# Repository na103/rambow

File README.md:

# RAMbow - 1Mbyte memory expansion for Rainbow 100
"RAMbow flexes memory muscle" was the headline of a hardware review in the Silicon Valley Rainbow bulletin in October 1987.<br>
The article, which you can read in full [here](https://github.com/na103/rambow/blob/main/docs/RAMbow.pdf), discusses a memory expansion designed by Jerry Miller and marketed by Suitable Solution.<br>
This expansion could extend the memory of the first version of the Rainbow 100 (revision A) beyond its design limit of 256KB.<br><br>

<br>
The Rainbow 100 initially came with only 64KB onboard, which could be expanded via the option RAM up to a maximum of 256KB.<br>
Later, DEC developed an 8087 adapter card that allowed the option RAM card of the Rainbow 100 B to be used in rev A, enabling memory expansion up to a maximum of 832KB with a sandwich installation.<br>
RAMbow combines the 8087 adapter and the option RAM of the Rainbow B into a single card, allowing 896KB of memory on the 100A.<br>
Inspired by this article, I modified [my remake of the option RAM rev. B](https://github.com/na103/rainbow100-memory) with a single 1MB DRAM bank, creating room to accommodate the 8088 CPU socket.<br>
Indeed the main problem with the 100A is that the expansion connector of the option RAM lacks the A16 to A19 address lines, necessitating the relocation of the CPU onto the memory card.<br>   
In this repository you will find all the information needed to build my interpretation of the legendary RAMbow (no schematics or picture exist the original board).<br>

## Bill of materials
| Qt. |    Description     |             Designator          |    Mouser Part     |             Note              |
|:---:|--------------------|---------------------------------|--------------------|-------------------------------|
|10   |Cap. 220 nF 50V     |C1-C9,C18                        |C430C224Z5U5TA      |                               |
|1    |Cap. 10uF 50V       |C17                              |MAL213831109E3      |                               |
|5    |Cap. 47nF 50V       |C12-C16                          |C410C473Z5U5TA      |                               |
|2    |Cap. 10nF 50V       |C10,C11                          |C410C103Z5U5TA      |                               |
|1    |Bead Ferrite        |FB1                              |2743002112          |                               |
|2    |Rnet 9x1kΩ 10 pin   |RN1,RN2                          |4610X-101-102LF     |                               |
|1    |Rnet 9x4.7kΩ 10 pin |RN3                              |4610X-AP1-472LF     |                               |
|10   |R 39Ω               |R2-R11                           |CFR-25JB-52-39R     |                               |
|3    |R 470Ω              |R12-R14                          |CFR-25JB-52-470R    |                               |
|1    |R 100Ω              |R1                               |CFR-25JR-52-100R    |                               |
|3    |R 47Ω               |R15-R17                          |CFR-25JB-52-47R     |                               |
|2    |2 pin header        |JP1,JP2                          |67996-102HLF        |                               |
|2    |2 pin jumper shunt  |JP1,JP2                          |SNT-100-BL-T        |                               |
|1    |025X025 REC 2X30P   |J1                               |5-102766-4          |                               |
|9    |18P DIP SKT         |E16-E24                          |1-2199298-5         |                               |
|1    |40P DIP SKT         |E26                              |1-2199299-5         |                               |
|1    |20P DIP SKT         |E28                              |1-2199298-6         |                               |
|1    |40P IDC CONN M      |J2                               |3-1761605-3         |                               |
|1    |40P DIP IDC SKT     |J2                               |CWR-130-40-0000     |                               |
|1    |40P IDC CONN F      |J2                               |D89140-0101HK       |                               |
|1    |40P IDC Flat cable  |J2                               |                    | you can use an old IDE cable  |
|1    |GAL 16V8            |E28                              |ATF16V8CZ-15PU      | need programmer like TL866    |
|2    |74LS04              |E1,E7                            |SN74LS04N           |                               |
|3    |74LS258             |E2,E3,E15                        |SN74LS258BN         |                               |
|2    |74LS393             |E4,E25                           |SN74LS393N          |                               |
|2    |74LS244             |E5,E14                           |SN74LS244N          |                               |
|1    |74LS245             |E6                               |SN7LS245N           |                               |
|1    |74LS27              |E8                               |SN74LS27N           |                               |
|1    |74LS280             |E9                               |SN74LS280N          |                               |
|1    |74LS125             |E10                              |SN74LS125AN         |                               |
|1    |74LS00              |E11                              |SN74LS00N           |                               |
|1    |74LS03              |E12                              |SN74LS03N           |                               |
|1    |74LS74              |E13                              |SN74LS74AN          |                               |
|1    |74LS373             |E27                              |SN74LS373N          |                               |
|9    |1Mbit DRAM 41024    |E16-E24                          |HM511000AP-8        | from ebay or [utsource](https://www.utsource.net)|

<br>

## Jumper set-up
Only a jumper need to setup, JP2 is closed when RAMbow is installed on rev A or open in rev B.<br>
JP1 is always closed.

## Building notes
As you can see from the picture the IDC cable of the J2 connector that is used to relocate the CPU requires a bit of attention in construction<br><br>
<br>
the length of the cable must be 85mm and you must separate the individual wires with a cutter to make the cable more flexible.<br>
the operation requires a little attention to avoid cutting the copper insulation.<br>
even closing the socket with pressure requires a fair amount of force, help yourself with some tool<br>

<br>

## Compatibility and issues

I have successfully tested RAMbow on rev. A and rev. B. with the following operating systems:<br>
MSDOS 3.10<br>
MSDOS 2.10<br>
CP/M-86/80 2.10<br>
CP/M-86/80 2.0<br>
I have not encountered any kind of problem, both rev A and rev B have 896Kb of memory available.<br>
After building RAMbow you can test it with the diagnostic software for memory expansion rev B that you can find [here](https://github.com/na103/rainbow100-memory/tree/main/software)<br><br>

## Thanks
Thankyou to all the people who have helped with this project.<br>
Bigfix for sharing the DEC schematics of the 8087 adapter.<br>
N. Brown and Alitel for actively participating with their ideas in the [VCFED forum thread.](https://forum.vcfed.org/index.php?threads/rainbow-100a-memory-beyond-256k.1247302/)<br>
Claudio Parmigiani for the valuable advice<br>

If you found this my work useful, please consider buying me a cup of coffee if you want:<br>

# License

This work is licensed under a Creative Commons Attribution 4.0 International License. See [https://creativecommons.org/licenses/by/4.0/](https://creativecommons.org/licenses/by/4.0/).

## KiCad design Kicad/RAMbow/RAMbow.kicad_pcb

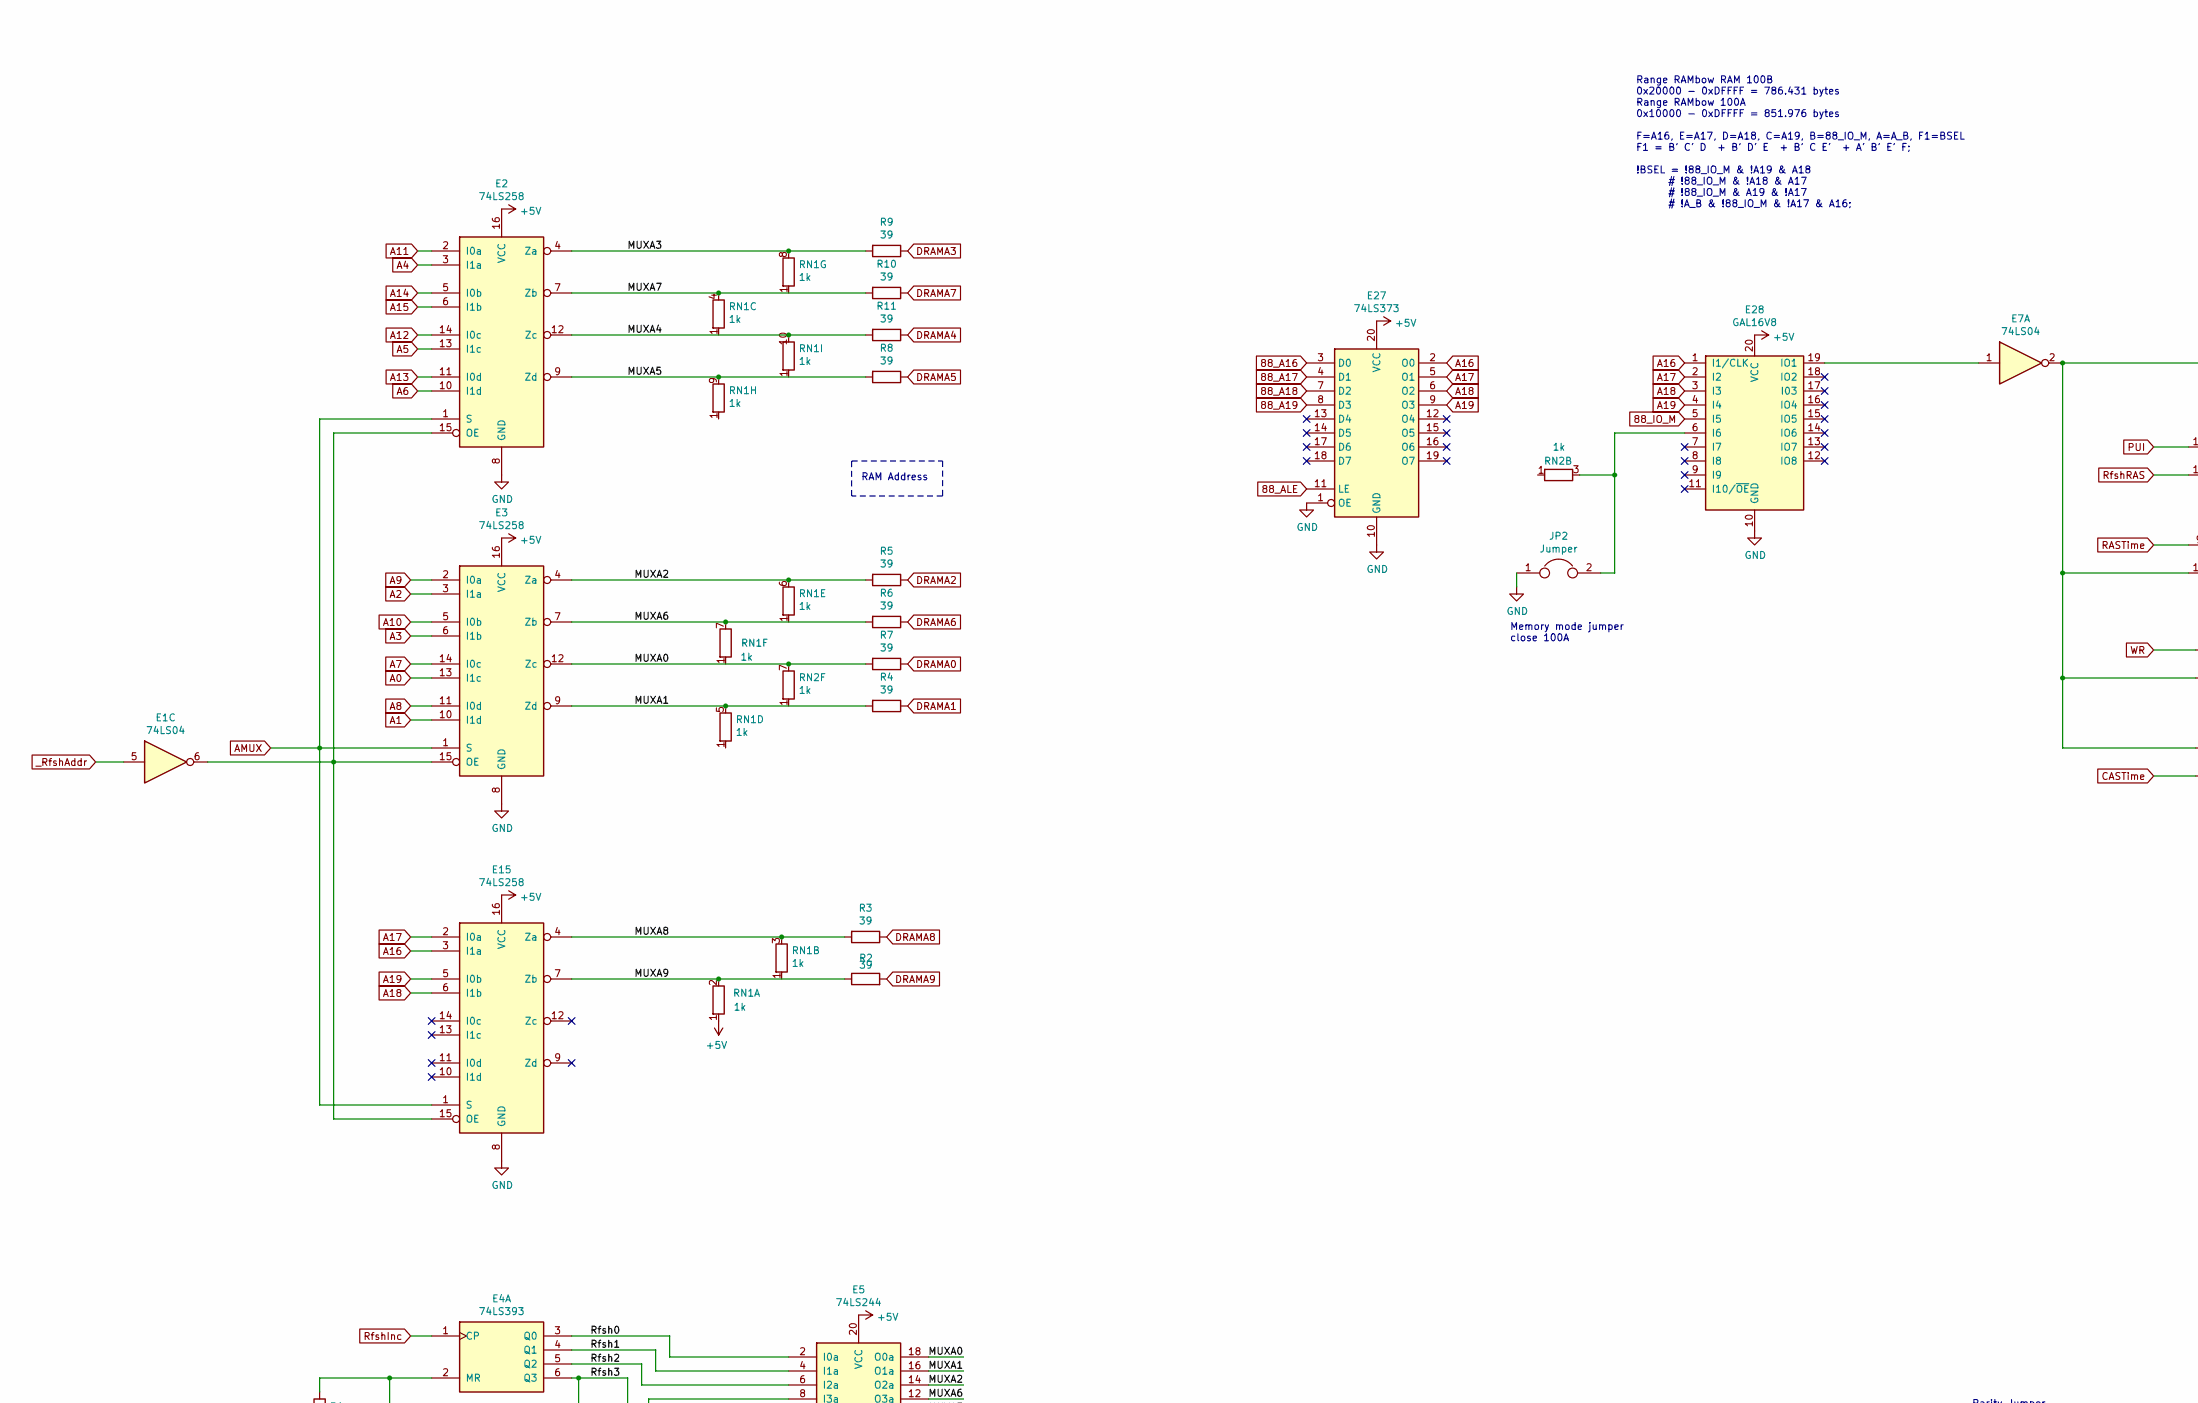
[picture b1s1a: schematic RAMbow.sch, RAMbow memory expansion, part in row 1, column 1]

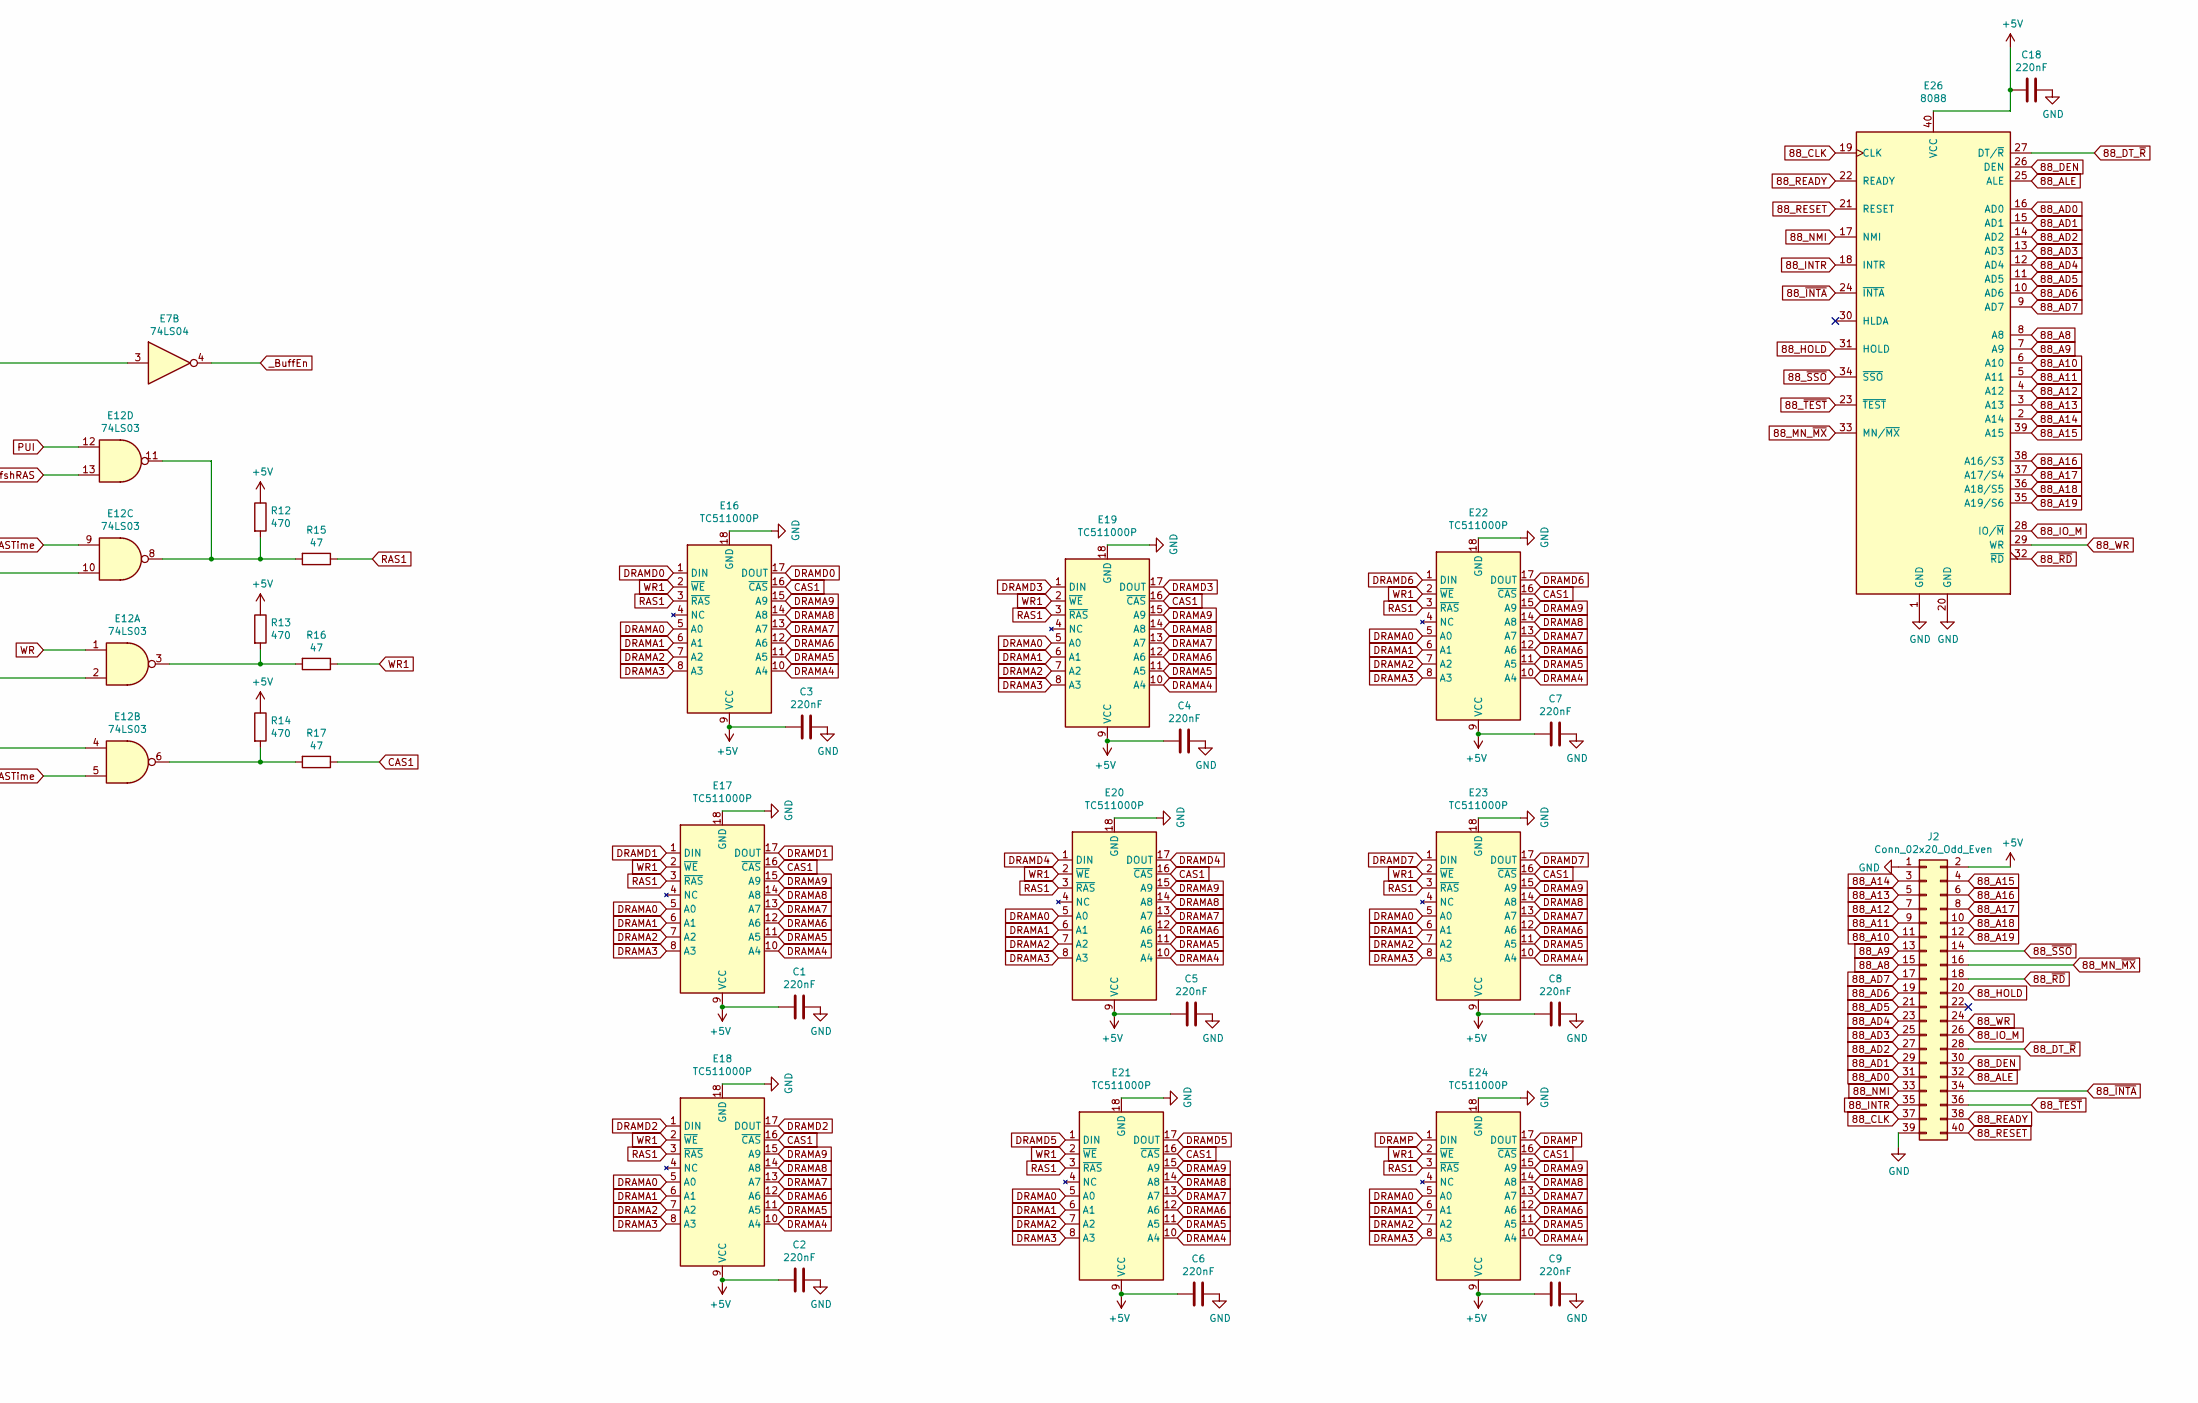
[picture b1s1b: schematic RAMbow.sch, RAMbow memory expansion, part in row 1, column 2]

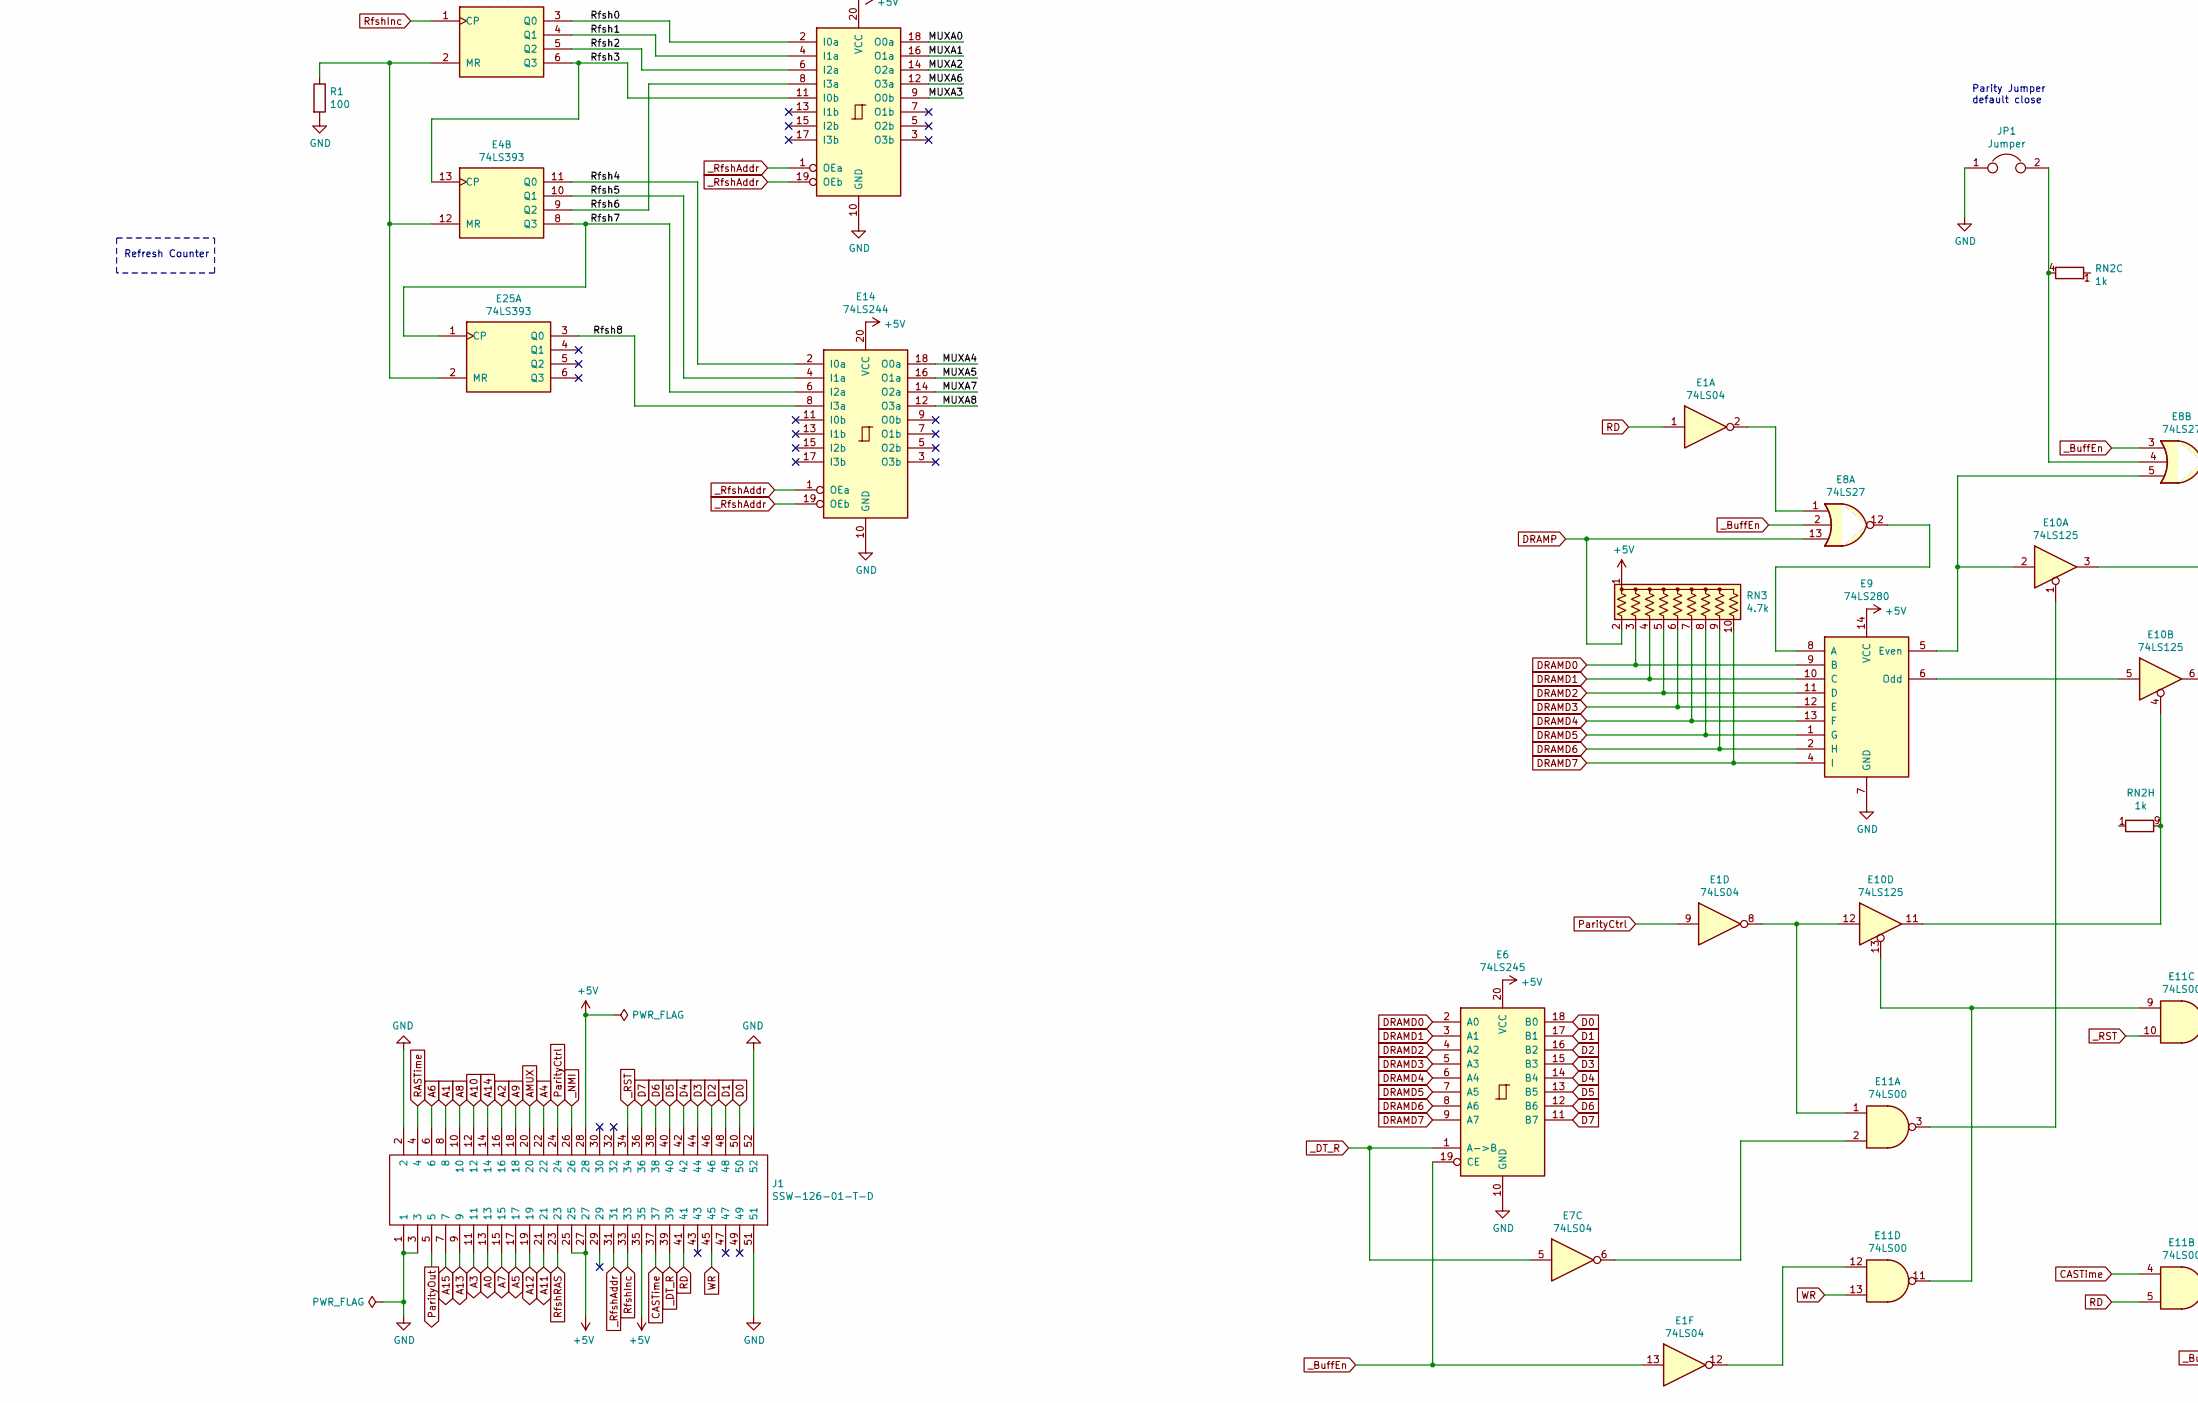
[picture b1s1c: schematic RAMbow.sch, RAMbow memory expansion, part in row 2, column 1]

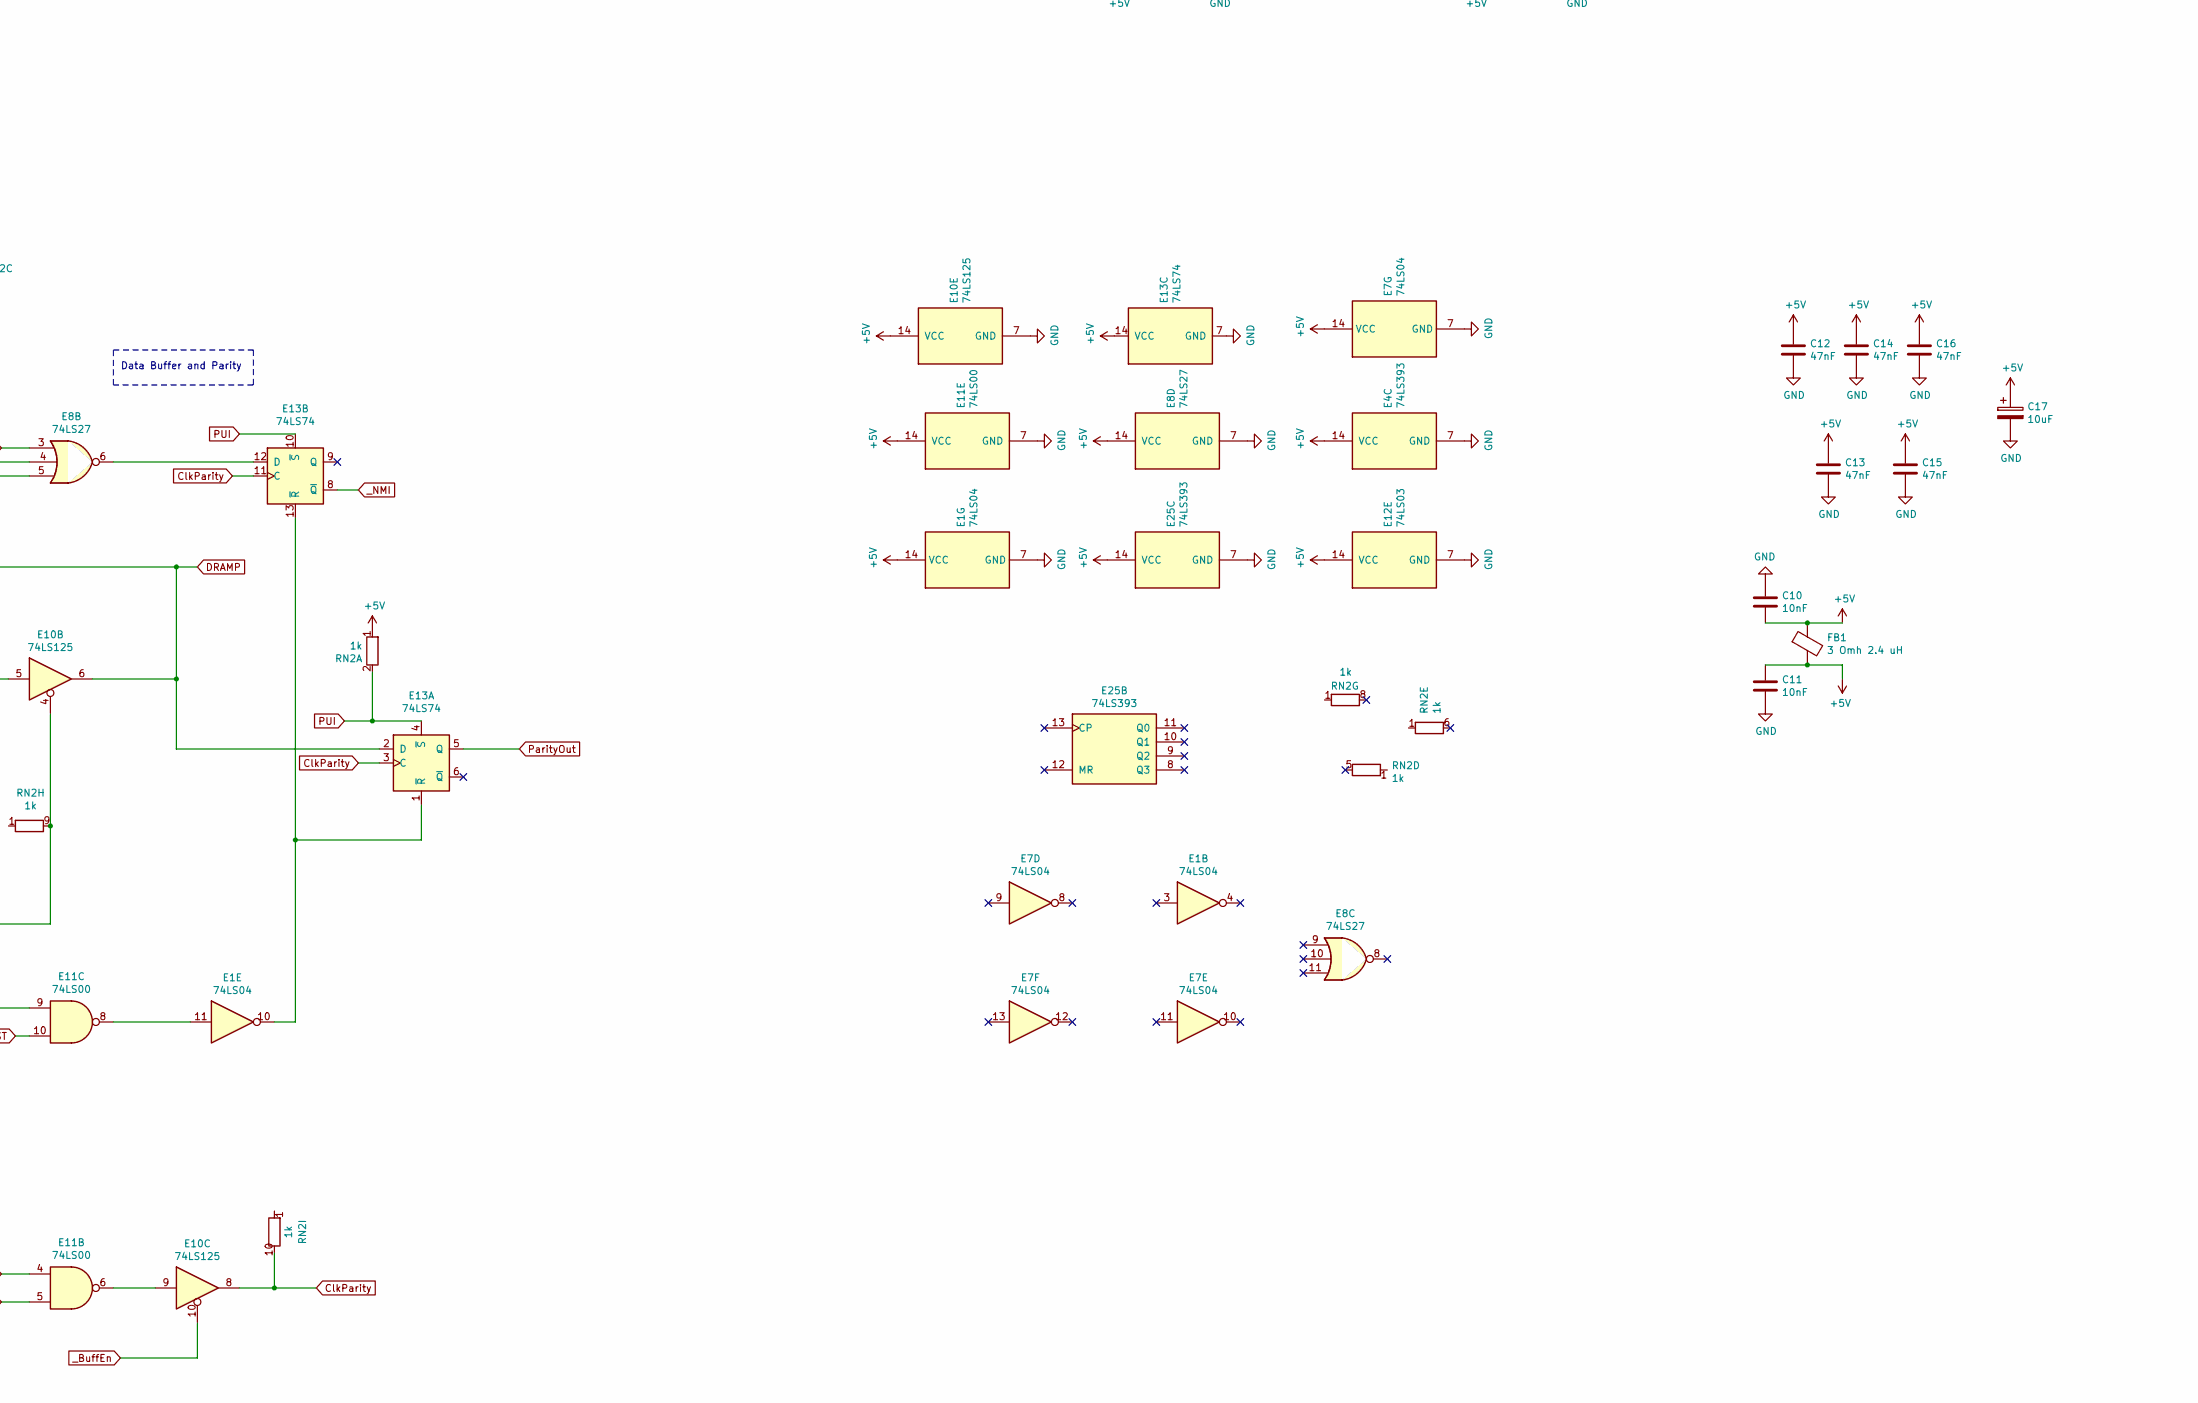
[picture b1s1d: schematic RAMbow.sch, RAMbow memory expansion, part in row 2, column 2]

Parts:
C1, C2, C3, C4, C5, C6, C7, C8, C9, C18: 220nF; C_Axial_L3.8mm_D2.6mm_P7.50mm_Horizontal
C10, C11: 10nF; C_Axial_L3.8mm_D2.6mm_P10.00mm_Horizontal
C12, C13, C14, C15, C16: 47nF; C_Axial_L3.8mm_D2.6mm_P10.00mm_Horizontal
C17: 10uF; C_Axial_L12.0mm_D6.5mm_P20.00mm_Horizontal
E1, E7: 74LS04; DIP-14_W7.62mm
E2, E3, E15: 74LS258; DIP-16_W7.62mm
E4, E25: 74LS393; DIP-14_W7.62mm
E5, E14: 74LS244; DIP-20_W7.62mm
E6: 74LS245; DIP-20_W7.62mm
E8: 74LS27; DIP-14_W7.62mm
E9: 74LS280; DIP-14_W7.62mm
E10: 74LS125; DIP-14_W7.62mm
E11: 74LS00; DIP-14_W7.62mm
E12: 74LS03; DIP-14_W7.62mm
E13: 74LS74; DIP-14_W7.62mm
E16, E17, E18, E19, E20, E21, E22, E23, E24: TC511000P; DIP-18_W7.62mm
E26: 8088; DIP-40_W15.24mm
E27: 74LS373; DIP-20_W7.62mm
E28: GAL16V8; DIP-20_W7.62mm
FB1: 3 Omh 2.4 uH; L_Axial_L9.5mm_D4.0mm_P15.24mm_Horizontal_Fastron_SMCC
J1: SSW-126-01-T-D; SAMTEC_SSW-126-01-T-D; Mouser Part Number 200-SSW12601TD
J2: Conn_02x20_Odd_Even; IDC-Header_2x20_P2.54mm_Horizontal
JP1, JP2: Jumper; PinHeader_1x02_P2.54mm_Vertical
R1: 100; R_Axial_DIN0207_L6.3mm_D2.5mm_P10.16mm_Horizontal
R2, R3, R4, R5, R6, R7, R8, R9, R10, R11: 39; R_Axial_DIN0207_L6.3mm_D2.5mm_P10.16mm_Horizontal
R12, R13, R14: 470; R_Axial_DIN0207_L6.3mm_D2.5mm_P10.16mm_Horizontal
R15, R16, R17: 47; R_Axial_DIN0207_L6.3mm_D2.5mm_P10.16mm_Horizontal
RN1, RN2: 1k; R_Array_SIP10
RN3: 4.7k; R_Array_SIP10

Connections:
88_A8: E26.8 (A8), J2.15
88_A9: E26.7 (A9), J2.13
88_A10: E26.6 (A10), J2.11
88_A11: E26.5 (A11), J2.9
88_A12: E26.4 (A12), J2.7
88_A13: E26.3 (A13), J2.5
88_A14: E26.2 (A14), J2.3
88_A15: E26.39 (A15), J2.4
88_A16: E26.38 (A16/S3), E27.3 (D0), J2.6
88_A17: E26.37 (A17/S4), E27.4 (D1), J2.8
88_A18: E26.36 (A18/S5), E27.7 (D2), J2.10
88_A19: E26.35 (A19/S6), E27.8 (D3), J2.12
88_AD0: E26.16 (AD0), J2.31
88_AD1: E26.15 (AD1), J2.29
88_AD2: E26.14 (AD2), J2.27
88_AD3: E26.13 (AD3), J2.25
88_AD4: E26.12 (AD4), J2.23
88_AD5: E26.11 (AD5), J2.21
88_AD6: E26.10 (AD6), J2.19
88_AD7: E26.9 (AD7), J2.17
88_ALE: E26.25 (ALE), E27.11 (LE), J2.32
88_CLK: E26.19 (CLK), J2.37
88_DEN: E26.26 (DEN), J2.30
88_DT_~R~: E26.27 (DT/~R~), J2.28
88_HOLD: E26.31 (HOLD), J2.20
88_INTR: E26.18 (INTR), J2.35
88_IO_M: E26.28 (IO/~M~), E28.5 (I5), J2.26
88_MN_~MX~: E26.33 (MN/~MX~), J2.16
88_NMI: E26.17 (NMI), J2.33
88_READY: E26.22 (READY), J2.38
88_RESET: E26.21 (RESET), J2.40
88_WR: E26.29 (WR), J2.24
88_~INTA~: E26.24 (~INTA~), J2.34
88_~RD~: E26.32 (~RD~), J2.18
88_~SSO~: E26.34 (~SSO~), J2.14
88_~TEST~: E26.23 (~TEST~), J2.36
+5V: C1.2, C2.2, C3.2, C4.2, C5.2, C6.2, C7.2, C8.2, C9.2, C10.2, C11.1, C12.1, C13.1, C14.1, C15.1, C16.1, C17.1, C18.2, E1.14 (VCC), E2.16 (VCC), E3.16 (VCC), E4.14 (VCC), E5.20 (VCC), E6.20 (VCC), E7.14 (VCC), E8.14 (VCC), E9.14 (VCC), E10.14 (VCC), E11.14 (VCC), E12.14 (VCC), E13.14 (VCC), E14.20 (VCC), E15.16 (VCC), E16.9 (VCC), E17.9 (VCC), E18.9 (VCC), E19.9 (VCC), E20.9 (VCC), E21.9 (VCC), E22.9 (VCC), E23.9 (VCC), E24.9 (VCC), E25.14 (VCC), E26.40 (VCC), E27.20 (VCC), E28.20 (VCC), FB1.1, FB1.2, J1.25, J1.27, J1.28, J1.35, J2.2, R12.1, R13.1, R14.1, RN1.1 (R1.1), RN2.1 (R1.1), RN3.1 (common)
/MUXA0: E3.12 (Zc), E5.18 (O0a), R7.2, RN2.7 (R6.2)
/MUXA1: E3.9 (Zd), E5.16 (O1a), R4.2, RN1.5 (R4.2)
/MUXA2: E3.4 (Za), E5.14 (O2a), R5.2, RN1.6 (R5.2)
/MUXA3: E2.4 (Za), E5.9 (O0b), R9.2, RN1.8 (R7.2)
/MUXA4: E2.12 (Zc), E14.18 (O0a), R11.2, RN1.10 (R9.2)
/MUXA5: E2.9 (Zd), E14.16 (O1a), R8.2, RN1.9 (R8.2)
/MUXA6: E3.7 (Zb), E5.12 (O3a), R6.2, RN1.7 (R6.2)
/MUXA7: E2.7 (Zb), E14.14 (O2a), R10.2, RN1.4 (R3.2)
/MUXA8: E14.12 (O3a), E15.4 (Za), R3.2, RN1.3 (R2.2)
/MUXA9: E15.7 (Zb), R2.1, RN1.2 (R1.2)
/Rfsh0: E4.3 (Q0), E5.2 (I0a)
/Rfsh1: E4.4 (Q1), E5.4 (I1a)
/Rfsh2: E4.5 (Q2), E5.6 (I2a)
/Rfsh3: E4.6 (Q3), E4.13 (CP), E5.11 (I0b)
/Rfsh4: E4.11 (Q0), E14.2 (I0a)
/Rfsh5: E4.10 (Q1), E14.4 (I1a)
/Rfsh6: E4.9 (Q2), E5.8 (I3a)
/Rfsh7: E4.8 (Q3), E14.6 (I2a), E25.1 (CP)
/Rfsh8: E14.8 (I3a), E25.3 (Q0)
A0: E3.13 (I1c), J1.13
A1: E3.10 (I1d), J1.8
A2: E3.3 (I1a), J1.16
A3: E3.6 (I1b), J1.11
A4: E2.3 (I1a), J1.22
A5: E2.13 (I1c), J1.17
A6: E2.10 (I1d), J1.6
A7: E3.14 (I0c), J1.15
A8: E3.11 (I0d), J1.10
A9: E3.2 (I0a), J1.18
A10: E3.5 (I0b), J1.12
A11: E2.2 (I0a), J1.21
A12: E2.14 (I0c), J1.19
A13: E2.11 (I0d), J1.9
A14: E2.5 (I0b), J1.14
A15: E2.6 (I1b), J1.7
A16: E15.3 (I1a), E27.2 (O0), E28.1 (I1/CLK)
A17: E15.2 (I0a), E27.5 (O1), E28.2 (I2)
A18: E15.6 (I1b), E27.6 (O2), E28.3 (I3)
A19: E15.5 (I0b), E27.9 (O3), E28.4 (I4)
AMUX: E2.1 (S), E3.1 (S), E15.1 (S), J1.20
CAS1: E16.16 (~CAS), E17.16 (~CAS), E18.16 (~CAS), E19.16 (~CAS), E20.16 (~CAS), E21.16 (~CAS), E22.16 (~CAS), E23.16 (~CAS), E24.16 (~CAS), R17.1
CASTime: E11.4, E12.5, J1.37
ClkParity: E10.8, E13.3 (C), E13.11 (C), RN2.10 (R9.2)
D0: E6.18 (B0), J1.50
D1: E6.17 (B1), J1.48
D2: E6.16 (B2), J1.46
D3: E6.15 (B3), J1.44
D4: E6.14 (B4), J1.42
D5: E6.13 (B5), J1.40
D6: E6.12 (B6), J1.38
D7: E6.11 (B7), J1.36
DRAMA0: E16.5 (A0), E17.5 (A0), E18.5 (A0), E19.5 (A0), E20.5 (A0), E21.5 (A0), E22.5 (A0), E23.5 (A0), E24.5 (A0), R7.1
DRAMA1: E16.6 (A1), E17.6 (A1), E18.6 (A1), E19.6 (A1), E20.6 (A1), E21.6 (A1), E22.6 (A1), E23.6 (A1), E24.6 (A1), R4.1
DRAMA2: E16.7 (A2), E17.7 (A2), E18.7 (A2), E19.7 (A2), E20.7 (A2), E21.7 (A2), E22.7 (A2), E23.7 (A2), E24.7 (A2), R5.1
DRAMA3: E16.8 (A3), E17.8 (A3), E18.8 (A3), E19.8 (A3), E20.8 (A3), E21.8 (A3), E22.8 (A3), E23.8 (A3), E24.8 (A3), R9.1
DRAMA4: E16.10 (A4), E17.10 (A4), E18.10 (A4), E19.10 (A4), E20.10 (A4), E21.10 (A4), E22.10 (A4), E23.10 (A4), E24.10 (A4), R11.1
DRAMA5: E16.11 (A5), E17.11 (A5), E18.11 (A5), E19.11 (A5), E20.11 (A5), E21.11 (A5), E22.11 (A5), E23.11 (A5), E24.11 (A5), R8.1
DRAMA6: E16.12 (A6), E17.12 (A6), E18.12 (A6), E19.12 (A6), E20.12 (A6), E21.12 (A6), E22.12 (A6), E23.12 (A6), E24.12 (A6), R6.1
DRAMA7: E16.13 (A7), E17.13 (A7), E18.13 (A7), E19.13 (A7), E20.13 (A7), E21.13 (A7), E22.13 (A7), E23.13 (A7), E24.13 (A7), R10.1
DRAMA8: E16.14 (A8), E17.14 (A8), E18.14 (A8), E19.14 (A8), E20.14 (A8), E21.14 (A8), E22.14 (A8), E23.14 (A8), E24.14 (A8), R3.1
DRAMA9: E16.15 (A9), E17.15 (A9), E18.15 (A9), E19.15 (A9), E20.15 (A9), E21.15 (A9), E22.15 (A9), E23.15 (A9), E24.15 (A9), R2.2
DRAMD0: E6.2 (A0), E9.9 (B), E16.1 (DIN), E16.17 (DOUT), RN3.3 (R2)
DRAMD1: E6.3 (A1), E9.10 (C), E17.1 (DIN), E17.17 (DOUT), RN3.4 (R3)
DRAMD2: E6.4 (A2), E9.11 (D), E18.1 (DIN), E18.17 (DOUT), RN3.5 (R4)
DRAMD3: E6.5 (A3), E9.12 (E), E19.1 (DIN), E19.17 (DOUT), RN3.6 (R5)
DRAMD4: E6.6 (A4), E9.13 (F), E20.1 (DIN), E20.17 (DOUT), RN3.7 (R6)
DRAMD5: E6.7 (A5), E9.1 (G), E21.1 (DIN), E21.17 (DOUT), RN3.8 (R7)
DRAMD6: E6.8 (A6), E9.2 (H), E22.1 (DIN), E22.17 (DOUT), RN3.9 (R8)
DRAMD7: E6.9 (A7), E9.4 (I), E23.1 (DIN), E23.17 (DOUT), RN3.10 (R9)
DRAMP: E8.13, E10.3, E10.6, E13.2 (D), E24.1 (DIN), E24.17 (DOUT), RN3.2 (R1)
GND: C1.1, C2.1, C3.1, C4.1, C5.1, C6.1, C7.1, C8.1, C9.1, C10.1, C11.2, C12.2, C13.2, C14.2, C15.2, C16.2, C17.2, C18.1, E1.7 (GND), E2.8 (GND), E3.8 (GND), E4.7 (GND), E5.10 (GND), E6.10 (GND), E7.7 (GND), E8.7 (GND), E9.7 (GND), E10.7 (GND), E11.7 (GND), E12.7 (GND), E13.7 (GND), E14.10 (GND), E15.8 (GND), E16.18 (GND), E17.18 (GND), E18.18 (GND), E19.18 (GND), E20.18 (GND), E21.18 (GND), E22.18 (GND), E23.18 (GND), E24.18 (GND), E25.7 (GND), E26.1 (GND), E26.20 (GND), E27.1 (OE), E27.10 (GND), E28.10 (GND), J1.1, J1.2, J1.3, J1.51, J1.52, J2.1, J2.39, JP1.1, JP2.1, R1.2
unnamed: E1.2, E8.1
unnamed: E1.6, E2.15 (OE), E3.15 (OE), E15.15 (OE)
unnamed: E1.8, E10.12, E11.1
unnamed: E1.10, E13.1 (~R), E13.13 (~R)
unnamed: E1.11, E11.8
unnamed: E1.12, E11.12
unnamed: E8.4, JP1.2, RN2.4 (R3.2)
unnamed: E8.12, E9.8 (A)
unnamed: E10.1, E11.3
unnamed: E8.5, E9.5 (Even), E10.2
unnamed: E9.6 (Odd), E10.5
unnamed: E10.9, E11.6
unnamed: E10.4, E10.11, RN2.9 (R8.2)
unnamed: E10.13, E11.9, E11.11
unnamed: E7.6, E11.2
unnamed: E12.3, R13.2, R16.2
unnamed: E12.6, R14.2, R17.2
unnamed: E7.2, E7.3, E12.2, E12.4, E12.10
unnamed: E12.8, E12.11, R12.2, R15.2
unnamed: E8.6, E13.12 (D)
unnamed: E4.2 (MR), E4.12 (MR), E25.2 (MR), R1.1
unnamed: E28.6 (I6), JP2.2, RN2.3 (R2.2)
unnamed: E7.1, E28.19 (IO1)
PUI: E12.12, E13.4 (~S), E13.10 (~S), RN2.2 (R1.2)
ParityCtrl: E1.9, J1.24
ParityOut: E13.5 (Q), J1.5
RAS1: E16.3 (~RAS), E17.3 (~RAS), E18.3 (~RAS), E19.3 (~RAS), E20.3 (~RAS), E21.3 (~RAS), E22.3 (~RAS), E23.3 (~RAS), E24.3 (~RAS), R15.1
RASTime: E12.9, J1.4
RD: E1.1, E11.5, J1.41
RfshInc: E4.1 (CP), J1.33
RfshRAS: E12.13, J1.23
WR: E11.13, E12.1, J1.45
WR1: E16.2 (~WE), E17.2 (~WE), E18.2 (~WE), E19.2 (~WE), E20.2 (~WE), E21.2 (~WE), E22.2 (~WE), E23.2 (~WE), E24.2 (~WE), R16.1
_BuffEn: E1.13, E6.19 (CE), E7.4, E8.2, E8.3, E10.10
_DT_R: E6.1 (A->B), E7.5, J1.39
_NMI: E13.8 (~Q), J1.26
_RST: E11.10, J1.34
_RfshAddr: E1.5, E5.1 (OEa), E5.19 (OEb), E14.1 (OEa), E14.19 (OEb), J1.31

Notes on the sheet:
Refresh Counter
Data Buffer and Parity
RAM Address
Range RAMbow RAM 100B 0x20000 - 0xDFFFF = 786.431 bytes Range RAMbow 100A 0x10000 - 0xDFFFF = 851.976 bytes F=A16, E=A17, D=A18, C=A19, B=88_IO_M, A=A_B, F1=BSEL F1 = B' C' D + B' D' E + B' C E' + A' B' E' F; !BSEL = !88_IO_M & !A19 & A18 # !88_IO_M & !A18 & A17 # !88_IO_M & A19 & !A17 # !A_B & !88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
Parity Jumper default close
Memory mode jumper close 100A

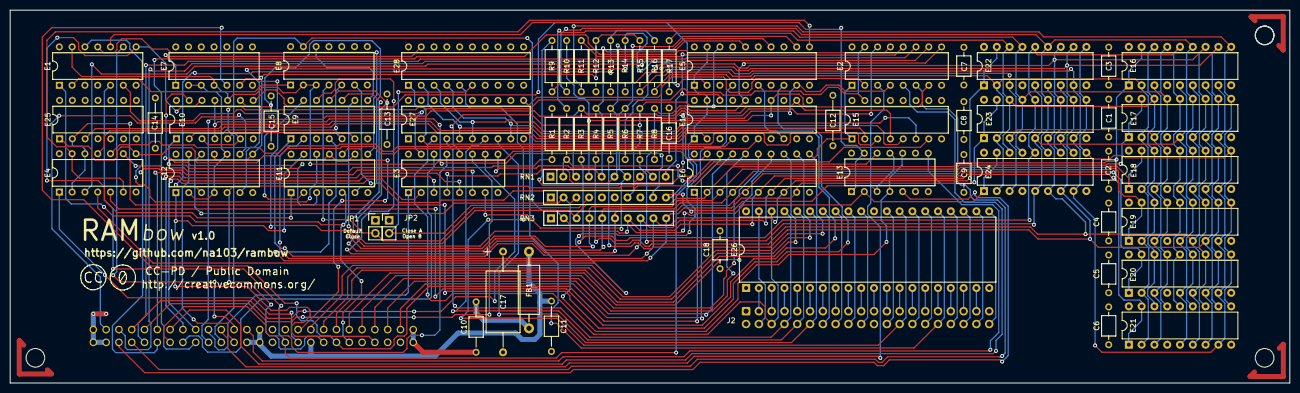
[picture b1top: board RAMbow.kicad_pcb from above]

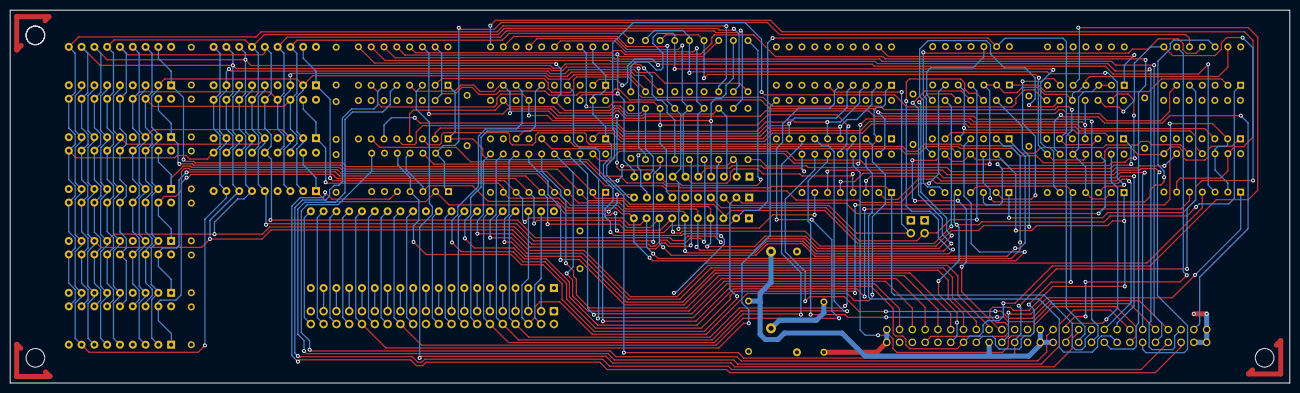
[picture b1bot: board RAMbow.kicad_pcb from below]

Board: 4 copper layers, 254.0 x 74.0 mm, 76 parts (2 on the bottom side), 146 nets.

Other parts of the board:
2, 3: MountingHole_3.7mm
CC: Symbol_CreativeCommonsPublicDomain_SilkScreenTop_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; Symbol_CreativeCommonsPublicDomain_SilkScreenTop_Small
H1, H3: MountingHole_3.7mm

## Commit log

2024-06-16 change img resolution
2024-06-16 test memory
2024-06-16 update img resolution
2024-06-16 GAL jed
2024-06-16 Kicad project + gerber file
2024-07-12 Create LICENSE
